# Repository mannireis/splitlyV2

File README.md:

# splitlyV2
A split keyboard I made a while ago but the pcb was wrong

| **Component**           | **Unit Cost** | **Procurement Status** | **Remarks**          |
| ----------------------- | ------------- | ---------------------- | -------------------- |
| **PCB**                 | **\$48.85**   | To be ordered          | Main board           |
| **Switches**            | \$0.00        | Already in stock       | No purchase needed   |
| **XIAO nRF**            | \$0.00        | Already in stock       | Microcontroller      |
| **Batteries**           | \$0.00        | Already in stock       | Power supply covered |
| **Custom Cable Pieces** | **\$30.83**   | To be ordered          | For connectivity     |

links

https://www.amazon.es/-/pt/dp/B0DS9MH1P8?crid=1P3Z7OZHVWUT6&dib=eyJ2IjoiMSJ9.71M58ZCOk5YEUdQg73kMnZ3M2RKFstADtkaf8pqHrkyubi4HHJ723iYT2V2pfQWhTampv_8W0J-YEuiKuM5F31oyY_RJ2BtH--225LMniLoEoT3krBGBQQXk3xHO06hisUPyQQ3zR8B4ws9kWFLw82BQrsEOevr96EWZKO1yMOzQQK93WopYPbBWJxDfwUKvG0bdZuPnC69oYiYmjuH07ihcz8mZGGHzoStmWCZOMALwj6ofWX45pe2BY2jEVIfAuia_fvjp1Z1WrXY4CmdN6UdsHx6mTU2PBHsE4vdBk_Y.VRDVyvNyllLLgWUE9EIOTDuavoYIKkgkIETlD2qdfvs&dib_tag=se&keywords=pink%2B550%2Bparacord%2Bsleeve&qid=1752082093&sprefix=pink%2B550%2Bparacord%2Bsleeve%2Caps%2C99&sr=8-1&th=1

https://pt.aliexpress.com/item/4000564519029.html?spm=a2g0o.productlist.main.2.435a7e29PTxfO8&algo_pvid=8722bdec-7039-4dea-a84a-f091a39dfb35&algo_exp_id=8722bdec-7039-4dea-a84a-f091a39dfb35-1&pdp_ext_f=%7B%22order%22%3A%22497%22%2C%22eval%22%3A%221%22%7D&pdp_npi=4%40dis%21EUR%213.52%213.52%21%21%214.03%214.03%21%402103868817520809549028833e526f%2112000044624314318%21sea%21PT%216399289739%21X&curPageLogUid=VpVX3jLsBKQP&utparam-url=scene%3Asearch%7Cquery_from%3A

https://pt.aliexpress.com/item/1005007265151286.html?spm=a2g0o.cart.0.0.5fc77f06niDN0t&mp=1&pdp_npi=5%40dis%21EUR%21EUR%201.41%21EUR%201.41%21%21EUR%201.41%21%21%21%40211b80d117520829030568485ee414%2112000039998021449%21ct%21PT%216399289739%21%211%210&gatewayAdapt=glo2bra

https://pt.aliexpress.com/item/1005007569115531.html?spm=a2g0o.productlist.main.4.49af58dbXtVXEv&aem_p4p_detail=202507091034552464897397418720010776915&algo_pvid=34b65443-82c3-4247-9a92-cdc2876ca89a&algo_exp_id=34b65443-82c3-4247-9a92-cdc2876ca89a-3&pdp_ext_f=%7B%22order%22%3A%22148%22%2C%22eval%22%3A%221%22%7D&pdp_npi=4%40dis%21EUR%213.50%213.50%21%21%2128.77%2128.77%21%402103835e17520824956172764e91f3%2112000041378541573%21sea%21PT%216399289739%21X&curPageLogUid=lF2vk9MQGfqT&utparam-url=scene%3Asearch%7Cquery_from%3A&search_p4p_id=202507091034552464897397418720010776915_1

https://pt.aliexpress.com/item/1005005579947177.html?spm=a2g0o.cart.0.0.5fc77f06Nr4og3&mp=1&pdp_npi=5%40dis%21EUR%21EUR%203.31%21EUR%202.85%21%21EUR%202.85%21%21%21%4021038df617521422048581561e9b70%2112000033628191688%21ct%21PT%216399289739%21%211%210&pdp_ext_f=%7B%22cart2PdpParams%22%3A%7B%22pdpBusinessMode%22%3A%22retail%22%7D%7D&gatewayAdapt=glo2bra

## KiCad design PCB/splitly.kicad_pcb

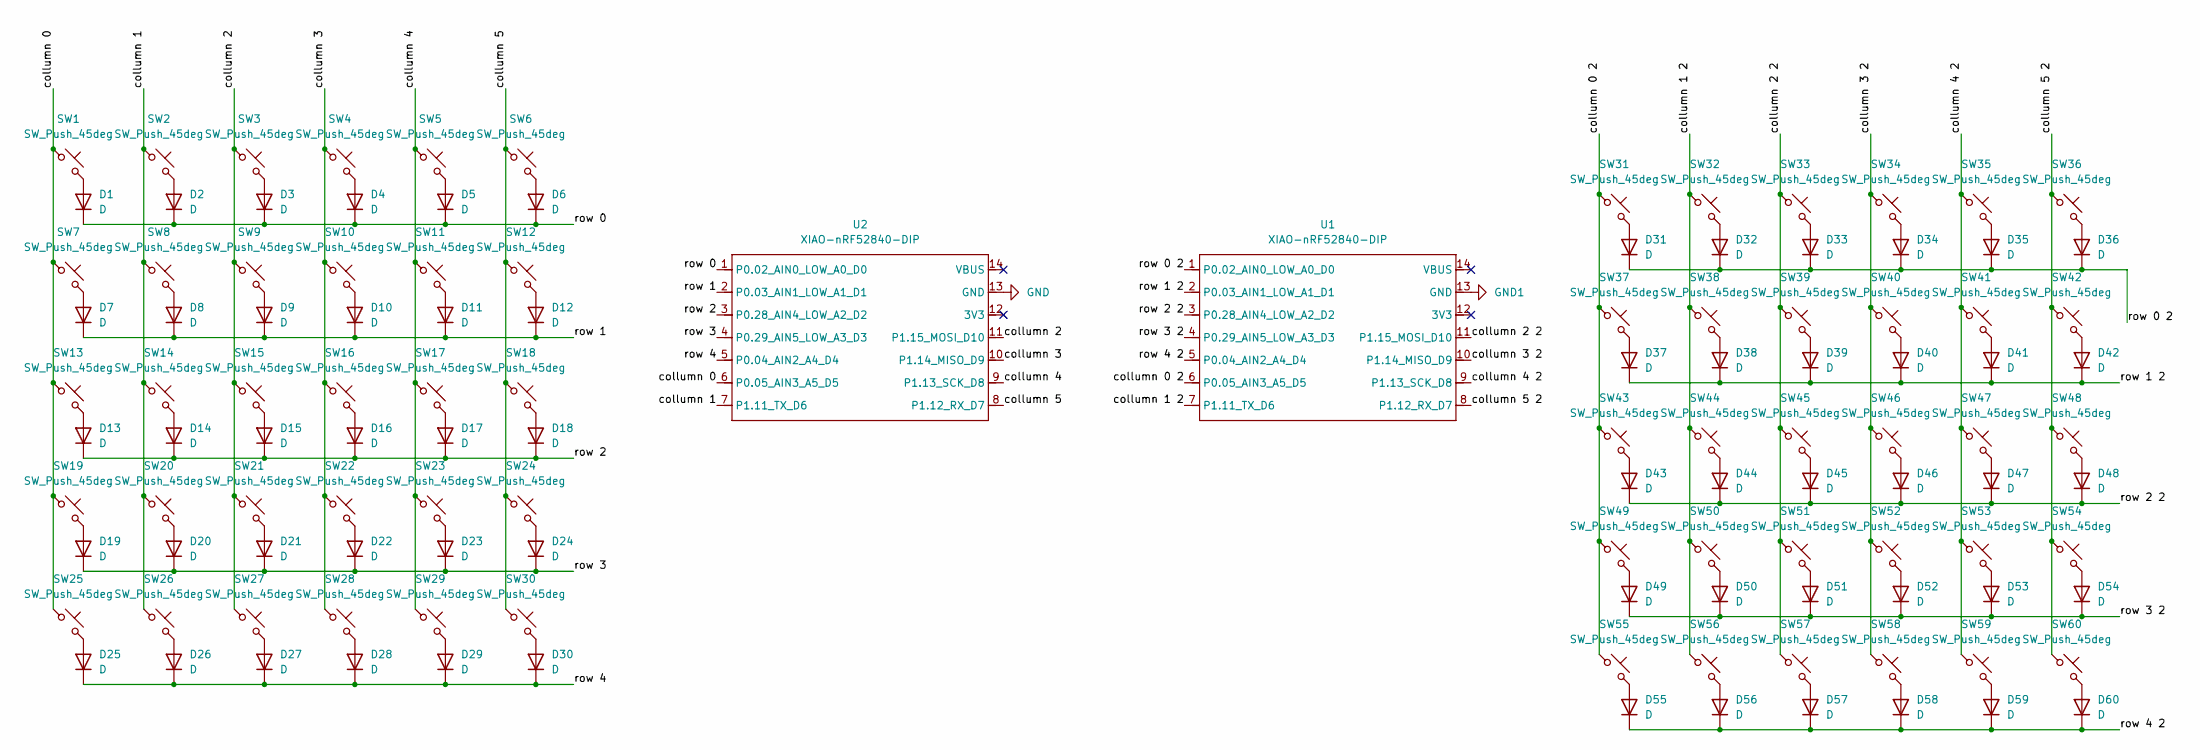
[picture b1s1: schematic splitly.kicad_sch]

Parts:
D1, D2, D3, D4, D5, D6, D7, D8, D9, D10, D11, D12, D13, D14, D15, D16, D17, D18, D19, D20, D21, D22, D23, D24, D25, D26, D27, D28, D29, D30, D31, D32, D33, D34, D35, D36, D37, D38, D39, D40, D41, D42, D43, D44, D45, D46, D47, D48, D49, D50, D51, D52, D53, D54, D55, D56, D57, D58, D59, D60: D; Diode_SOD-123
SW1, SW2, SW3, SW4, SW5, SW6, SW7, SW8, SW9, SW10, SW11, SW12, SW13, SW14, SW15, SW16, SW17, SW18, SW19, SW20, SW21, SW22, SW23, SW24, SW25, SW26, SW27, SW28, SW29, SW30, SW31, SW32, SW33, SW34, SW35, SW36, SW37, SW38, SW39, SW40, SW41, SW42, SW43, SW44, SW45, SW46, SW47, SW48, SW49, SW50, SW51, SW52, SW53, SW54, SW55, SW56, SW57, SW58, SW59, SW60: SW_Push_45deg; Hotswap_Choc_V1V2_1.00u
U1, U2: XIAO-nRF52840-DIP

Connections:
/collumn 0: SW1.1, SW7.1, SW13.1, SW19.1, SW25.1, U2.6 (P0.05_AIN3_A5_D5)
/collumn 0 2: SW31.1, SW37.1, SW43.1, SW49.1, SW55.1, U1.6 (P0.05_AIN3_A5_D5)
/collumn 1: SW2.1, SW8.1, SW14.1, SW20.1, SW26.1, U2.7 (P1.11_TX_D6)
/collumn 1 2: SW32.1, SW38.1, SW44.1, SW50.1, SW56.1, U1.7 (P1.11_TX_D6)
/collumn 2: SW3.1, SW9.1, SW15.1, SW21.1, SW27.1, U2.11 (P1.15_MOSI_D10)
/collumn 2 2: SW33.1, SW39.1, SW45.1, SW51.1, SW57.1, U1.11 (P1.15_MOSI_D10)
/collumn 3: SW4.1, SW10.1, SW16.1, SW22.1, SW28.1, U2.10 (P1.14_MISO_D9)
/collumn 3 2: SW34.1, SW40.1, SW46.1, SW52.1, SW58.1, U1.10 (P1.14_MISO_D9)
/collumn 4: SW5.1, SW11.1, SW17.1, SW23.1, SW29.1, U2.9 (P1.13_SCK_D8)
/collumn 4 2: SW35.1, SW41.1, SW47.1, SW53.1, SW59.1, U1.9 (P1.13_SCK_D8)
/collumn 5: SW6.1, SW12.1, SW18.1, SW24.1, SW30.1, U2.8 (P1.12_RX_D7)
/collumn 5 2: SW36.1, SW42.1, SW48.1, SW54.1, SW60.1, U1.8 (P1.12_RX_D7)
/row 0: D1.1 (K), D2.1 (K), D3.1 (K), D4.1 (K), D5.1 (K), D6.1 (K), U2.1 (P0.02_AIN0_LOW_A0_D0)
/row 0 2: D31.1 (K), D32.1 (K), D33.1 (K), D34.1 (K), D35.1 (K), D36.1 (K), U1.1 (P0.02_AIN0_LOW_A0_D0)
/row 1: D7.1 (K), D8.1 (K), D9.1 (K), D10.1 (K), D11.1 (K), D12.1 (K), U2.2 (P0.03_AIN1_LOW_A1_D1)
/row 1 2: D37.1 (K), D38.1 (K), D39.1 (K), D40.1 (K), D41.1 (K), D42.1 (K), U1.2 (P0.03_AIN1_LOW_A1_D1)
/row 2: D13.1 (K), D14.1 (K), D15.1 (K), D16.1 (K), D17.1 (K), D18.1 (K), U2.3 (P0.28_AIN4_LOW_A2_D2)
/row 2 2: D43.1 (K), D44.1 (K), D45.1 (K), D46.1 (K), D47.1 (K), D48.1 (K), U1.3 (P0.28_AIN4_LOW_A2_D2)
/row 3: D19.1 (K), D20.1 (K), D21.1 (K), D22.1 (K), D23.1 (K), D24.1 (K), U2.4 (P0.29_AIN5_LOW_A3_D3)
/row 3 2: D49.1 (K), D50.1 (K), D51.1 (K), D52.1 (K), D53.1 (K), D54.1 (K), U1.4 (P0.29_AIN5_LOW_A3_D3)
/row 4: D25.1 (K), D26.1 (K), D27.1 (K), D28.1 (K), D29.1 (K), D30.1 (K), U2.5 (P0.04_AIN2_A4_D4)
/row 4 2: D55.1 (K), D56.1 (K), D57.1 (K), D58.1 (K), D59.1 (K), D60.1 (K), U1.5 (P0.04_AIN2_A4_D4)
GND: U2.13 (GND)
GND1: U1.13 (GND)
unnamed: D1.2 (A), SW1.2
unnamed: D2.2 (A), SW2.2
unnamed: D3.2 (A), SW3.2
unnamed: D4.2 (A), SW4.2
unnamed: D5.2 (A), SW5.2
unnamed: D6.2 (A), SW6.2
unnamed: D7.2 (A), SW7.2
unnamed: D8.2 (A), SW8.2
unnamed: D9.2 (A), SW9.2
unnamed: D10.2 (A), SW10.2
unnamed: D11.2 (A), SW11.2
unnamed: D12.2 (A), SW12.2
unnamed: D13.2 (A), SW13.2
unnamed: D14.2 (A), SW14.2
unnamed: D15.2 (A), SW15.2
unnamed: D16.2 (A), SW16.2
unnamed: D17.2 (A), SW17.2
unnamed: D18.2 (A), SW18.2
unnamed: D19.2 (A), SW19.2
unnamed: D20.2 (A), SW20.2
unnamed: D21.2 (A), SW21.2
unnamed: D22.2 (A), SW22.2
unnamed: D23.2 (A), SW23.2
unnamed: D24.2 (A), SW24.2
unnamed: D25.2 (A), SW25.2
unnamed: D26.2 (A), SW26.2
unnamed: D27.2 (A), SW27.2
unnamed: D28.2 (A), SW28.2
unnamed: D29.2 (A), SW29.2
unnamed: D30.2 (A), SW30.2
unnamed: D31.2 (A), SW31.2
unnamed: D32.2 (A), SW32.2
unnamed: D33.2 (A), SW33.2
unnamed: D34.2 (A), SW34.2
unnamed: D35.2 (A), SW35.2
unnamed: D36.2 (A), SW36.2
unnamed: D37.2 (A), SW37.2
unnamed: D38.2 (A), SW38.2
unnamed: D39.2 (A), SW39.2
unnamed: D40.2 (A), SW40.2
unnamed: D41.2 (A), SW41.2
unnamed: D42.2 (A), SW42.2
unnamed: D43.2 (A), SW43.2
unnamed: D44.2 (A), SW44.2
unnamed: D45.2 (A), SW45.2
unnamed: D46.2 (A), SW46.2
unnamed: D47.2 (A), SW47.2
unnamed: D48.2 (A), SW48.2
unnamed: D49.2 (A), SW49.2
unnamed: D50.2 (A), SW50.2
unnamed: D51.2 (A), SW51.2
unnamed: D52.2 (A), SW52.2
unnamed: D53.2 (A), SW53.2
unnamed: D54.2 (A), SW54.2
unnamed: D55.2 (A), SW55.2
unnamed: D56.2 (A), SW56.2
unnamed: D57.2 (A), SW57.2
unnamed: D58.2 (A), SW58.2
unnamed: D59.2 (A), SW59.2
unnamed: D60.2 (A), SW60.2

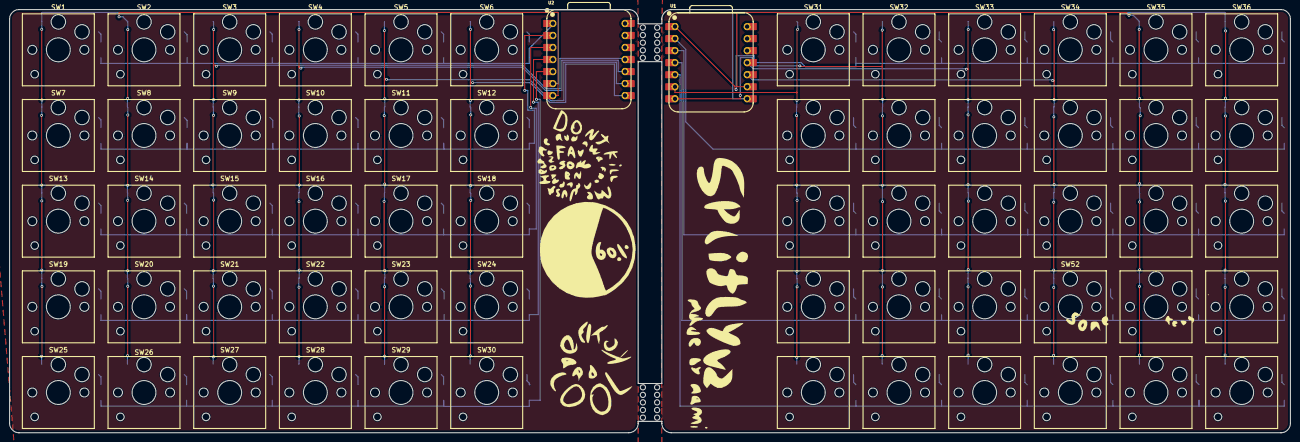
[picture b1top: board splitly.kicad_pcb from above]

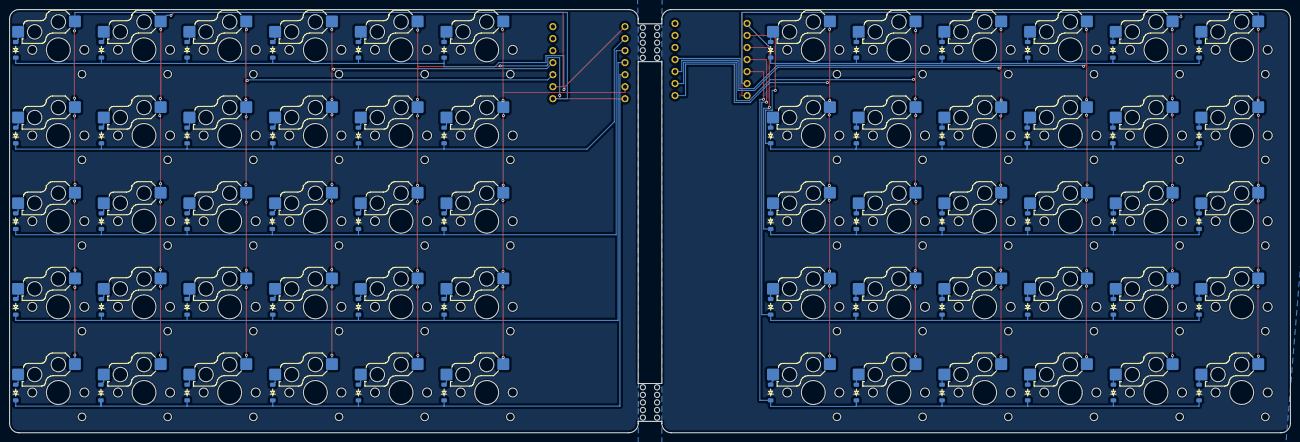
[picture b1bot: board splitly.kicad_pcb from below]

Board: 2 copper layers, 270.6 x 89.4 mm, 122 parts (60 on the bottom side), 82 nets.

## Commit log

2025-07-10 test?
